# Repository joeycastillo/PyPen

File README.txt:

PyPen Project

Very WIP. See here: https://twitter.com/josecastillo/status/1503400227864301573

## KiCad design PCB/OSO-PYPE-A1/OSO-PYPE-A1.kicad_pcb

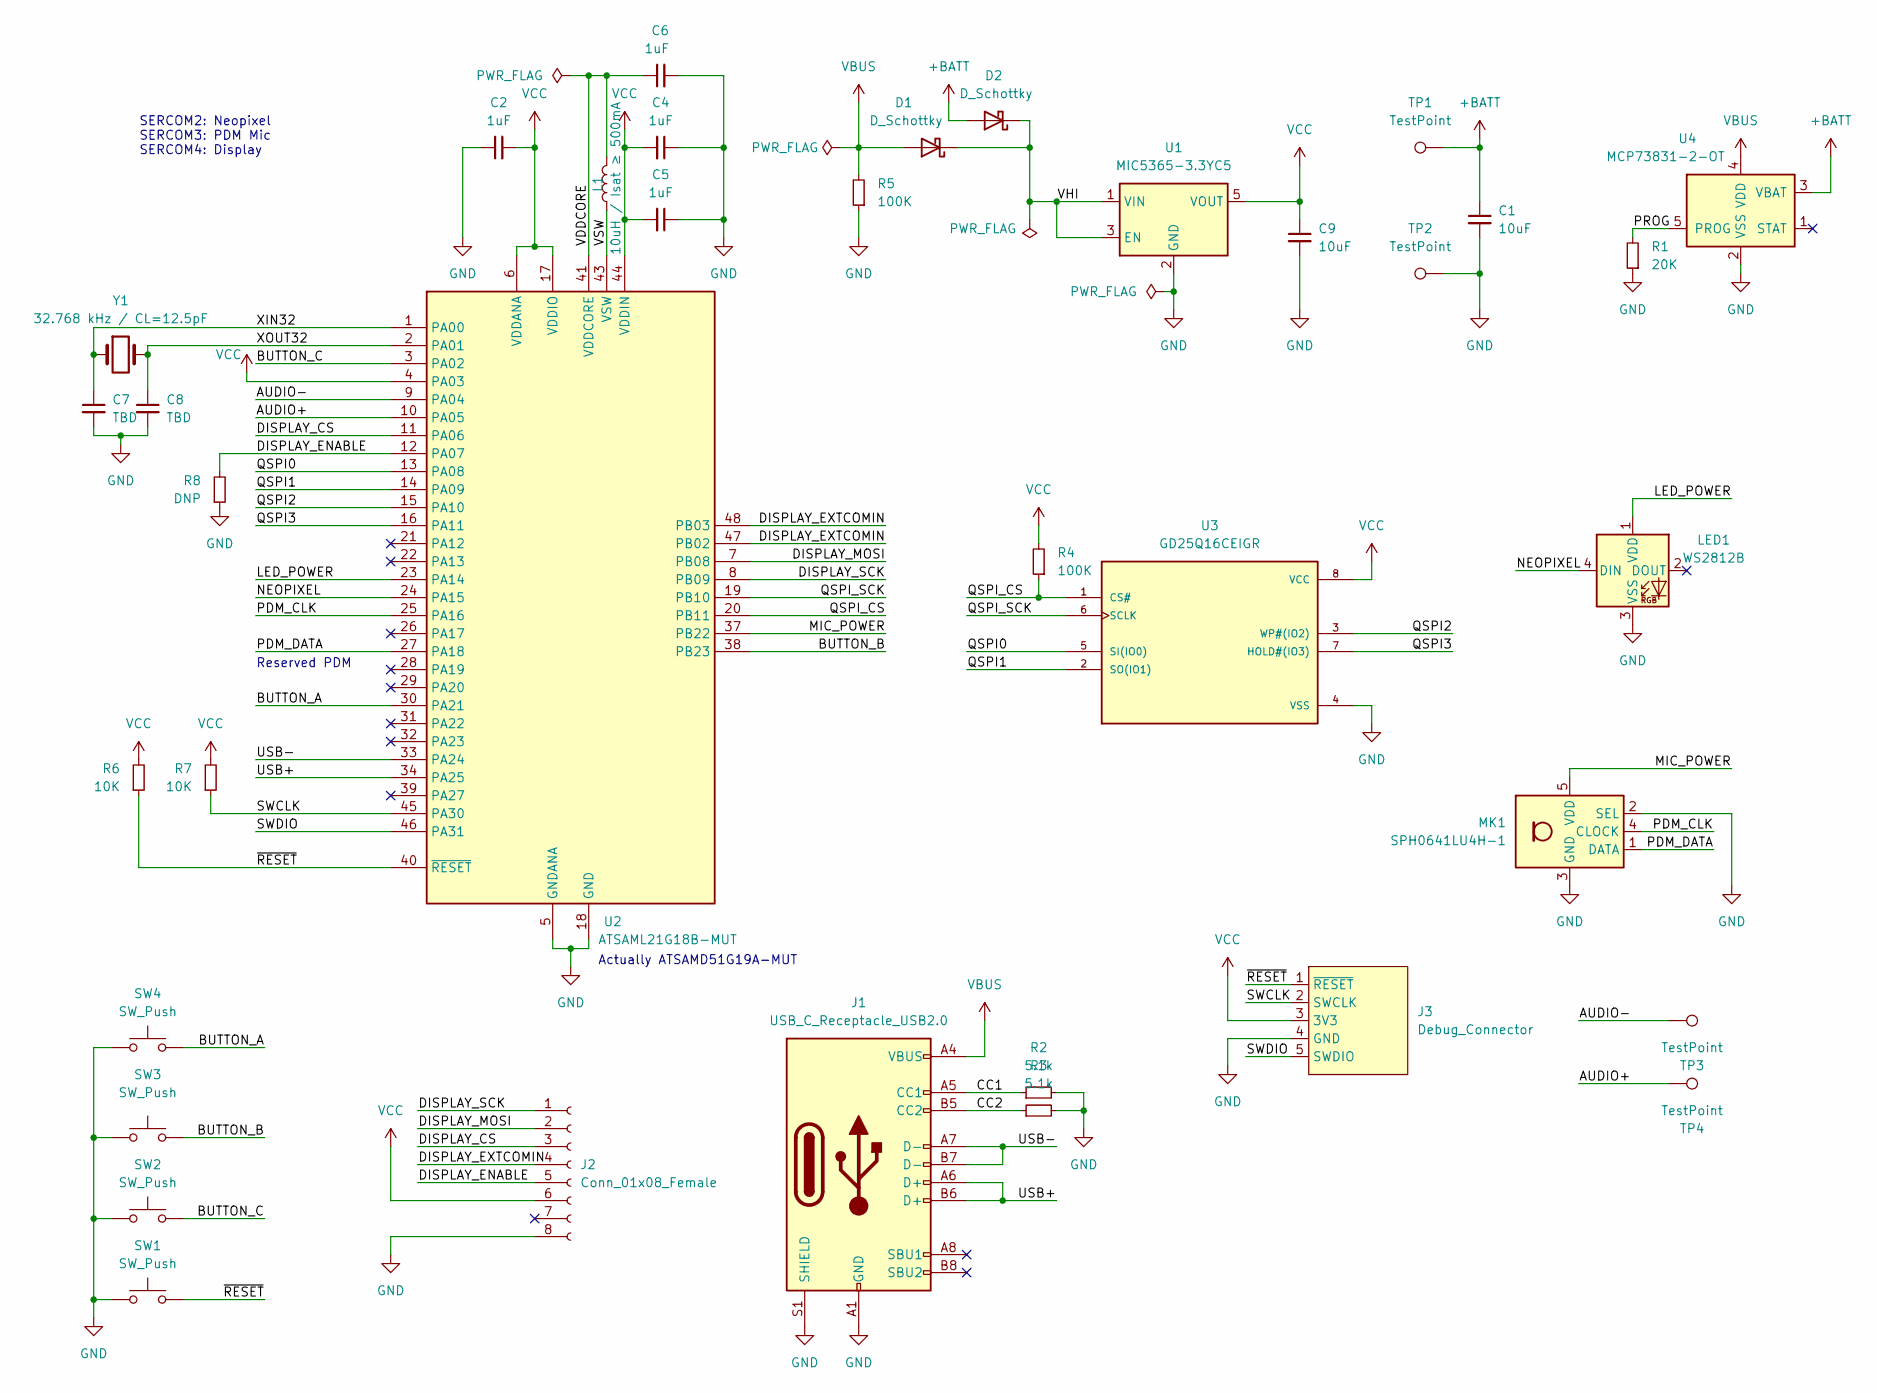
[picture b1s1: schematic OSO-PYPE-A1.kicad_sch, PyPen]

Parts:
C1, C9: 10uF; C_0603_1608Metric
C2, C4, C5, C6: 1uF; C_0603_1608Metric
C7, C8: TBD; C_0603_1608Metric
D1, D2: D_Schottky; D_SOD-323
J1: USB_C_Receptacle_USB2.0; USB_C_Receptacle_HRO_TYPE-C-31-M-12
J2: Conn_01x08_Female; TE_0-1734839-8_1x08-1MP_P0.5mm_Horizontal
J3: Debug_Connector; Debug_Connector_Stacked
L1: 10uH / Isat ≥ 500mA; L_0805_2012Metric
LED1: WS2812B; LED_WS2812B_2.0x2.0mm
MK1: SPH0641LU4H-1; Knowles_LGA-5_3.5x2.65mm
R1: 20K; R_0603_1608Metric
R2, R3: 5.1k; R_0603_1608Metric
R4, R5: 100K; R_0603_1608Metric
R6, R7: 10K; R_0603_1608Metric
R8: DNP; R_0603_1608Metric
SW1: SW_Push; Panasonic_EVQPUJ_EVQPUA
SW2, SW3, SW4: SW_Push; SW_Push_1P1T_NO_CK_KMR2
TP1, TP2: TestPoint; TestPoint_Keystone_5019_Minature
TP3, TP4: TestPoint; TestPoint_Pad_D1.0mm
U1: MIC5365-3.3YC5; SOT-353_SC-70-5
U2: ATSAML21G18B-MUT; QFN-48-1EP_7x7mm_P0.5mm_EP5.15x5.15mm
U3: GD25Q16CEIGR; PSON50P200X300X50-9N; PARTREV 3.0
U4: MCP73831-2-OT; SOT-23-5
Y1: 32.768 kHz / CL=12.5pF; Crystal_SMD_2012-2Pin_2.0x1.2mm

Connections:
+BATT: C1.1, D2.2 (A), TP1.1, U4.3 (VBAT)
/AUDIO+: TP4.1, U2.10 (PA05)
/AUDIO-: TP3.1, U2.9 (PA04)
/BUTTON_A: SW4.2, U2.30 (PA21)
/BUTTON_B: SW3.2, U2.38 (PB23)
/BUTTON_C: SW2.2, U2.3 (PA02)
/CC1: J1.A5 (CC1), R2.1
/CC2: J1.B5 (CC2), R3.1
/DISPLAY_CS: J2.3, U2.11 (PA06)
/DISPLAY_ENABLE: J2.5, R8.2, U2.12 (PA07)
/DISPLAY_EXTCOMIN: J2.4, U2.47 (PB02), U2.48 (PB03)
/DISPLAY_MOSI: J2.2, U2.7 (PB08)
/DISPLAY_SCK: J2.1, U2.8 (PB09)
/LED_POWER: LED1.1 (VDD), U2.23 (PA14)
/MIC_POWER: MK1.5 (VDD), U2.37 (PB22)
/NEOPIXEL: LED1.4 (DIN), U2.24 (PA15)
/PDM_CLK: MK1.4 (CLOCK), U2.25 (PA16)
/PDM_DATA: MK1.1 (DATA), U2.27 (PA18)
/PROG: R1.2, U4.5 (PROG)
/QSPI0: U2.13 (PA08), U3.5 (SI(IO0))
/QSPI1: U2.14 (PA09), U3.2 (SO(IO1))
/QSPI2: U2.15 (PA10), U3.3 (WP#(IO2))
/QSPI3: U2.16 (PA11), U3.7 (HOLD#(IO3))
/QSPI_CS: R4.1, U2.20 (PB11), U3.1 (CS#)
/QSPI_SCK: U2.19 (PB10), U3.6 (SCLK)
/SWCLK: J3.2 (SWCLK), R7.1, U2.45 (PA30)
/SWDIO: J3.5 (SWDIO), U2.46 (PA31)
/USB+: J1.A6 (D+), J1.B6 (D+), U2.34 (PA25)
/USB-: J1.A7 (D-), J1.B7 (D-), U2.33 (PA24)
/VDDCORE: C6.1, L1.2, U2.41 (VDDCORE)
/VHI: D1.1 (K), D2.1 (K), U1.1 (VIN), U1.3 (EN)
/VSW: L1.1, U2.43 (VSW)
/XIN32: C7.1, U2.1 (PA00), Y1.1
/XOUT32: C8.1, U2.2 (PA01), Y1.2
/~RESET: J3.1 (~RESET), R6.1, SW1.2, U2.40 (~RESET)
GND: C1.2, C2.1, C4.1, C5.1, C6.2, C7.2, C8.2, C9.2, J1.A1 (GND), J1.A12 (GND), J1.B1 (GND), J1.B12 (GND), J1.S1 (SHIELD), J2.8, J3.4 (GND), LED1.3 (VSS), MK1.2 (SEL), MK1.3 (GND), R1.1, R2.2, R3.2, R5.1, R8.1, SW1.1, SW2.1, SW3.1, SW4.1, TP2.1, U1.2 (GND), U2.5 (GNDANA), U2.18 (GND), U2.35 (GND), U2.42 (GND), U2.49, U3.4 (VSS), U4.2 (VSS)
VBUS: D1.2 (A), J1.A4 (VBUS), J1.A9 (VBUS), J1.B4 (VBUS), J1.B9 (VBUS), R5.2, U4.4 (VDD)
VCC: C2.2, C4.2, C5.2, C9.1, J2.6, J3.3 (3V3), R4.2, R6.2, R7.2, U1.5 (VOUT), U2.4 (PA03), U2.6 (VDDANA), U2.17 (VDDIO), U2.36 (VDDIO), U2.44 (VDDIN), U3.8 (VCC)

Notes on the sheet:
SERCOM2: Neopixel SERCOM3: PDM Mic SERCOM4: Display
Actually ATSAMD51G19A-MUT
Reserved PDM

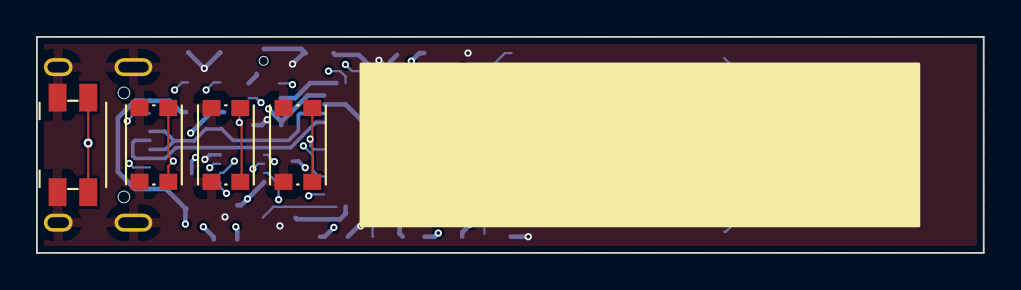
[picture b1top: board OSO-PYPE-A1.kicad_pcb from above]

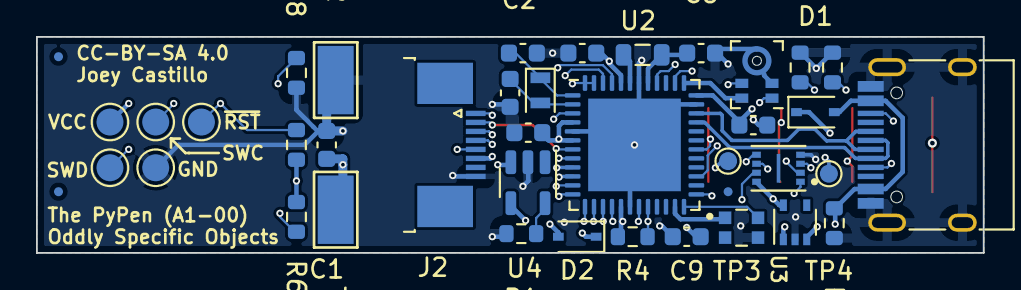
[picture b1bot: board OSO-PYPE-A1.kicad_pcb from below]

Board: 6 copper layers, 52.6 x 12.0 mm, 37 parts (33 on the bottom side), 38 nets.

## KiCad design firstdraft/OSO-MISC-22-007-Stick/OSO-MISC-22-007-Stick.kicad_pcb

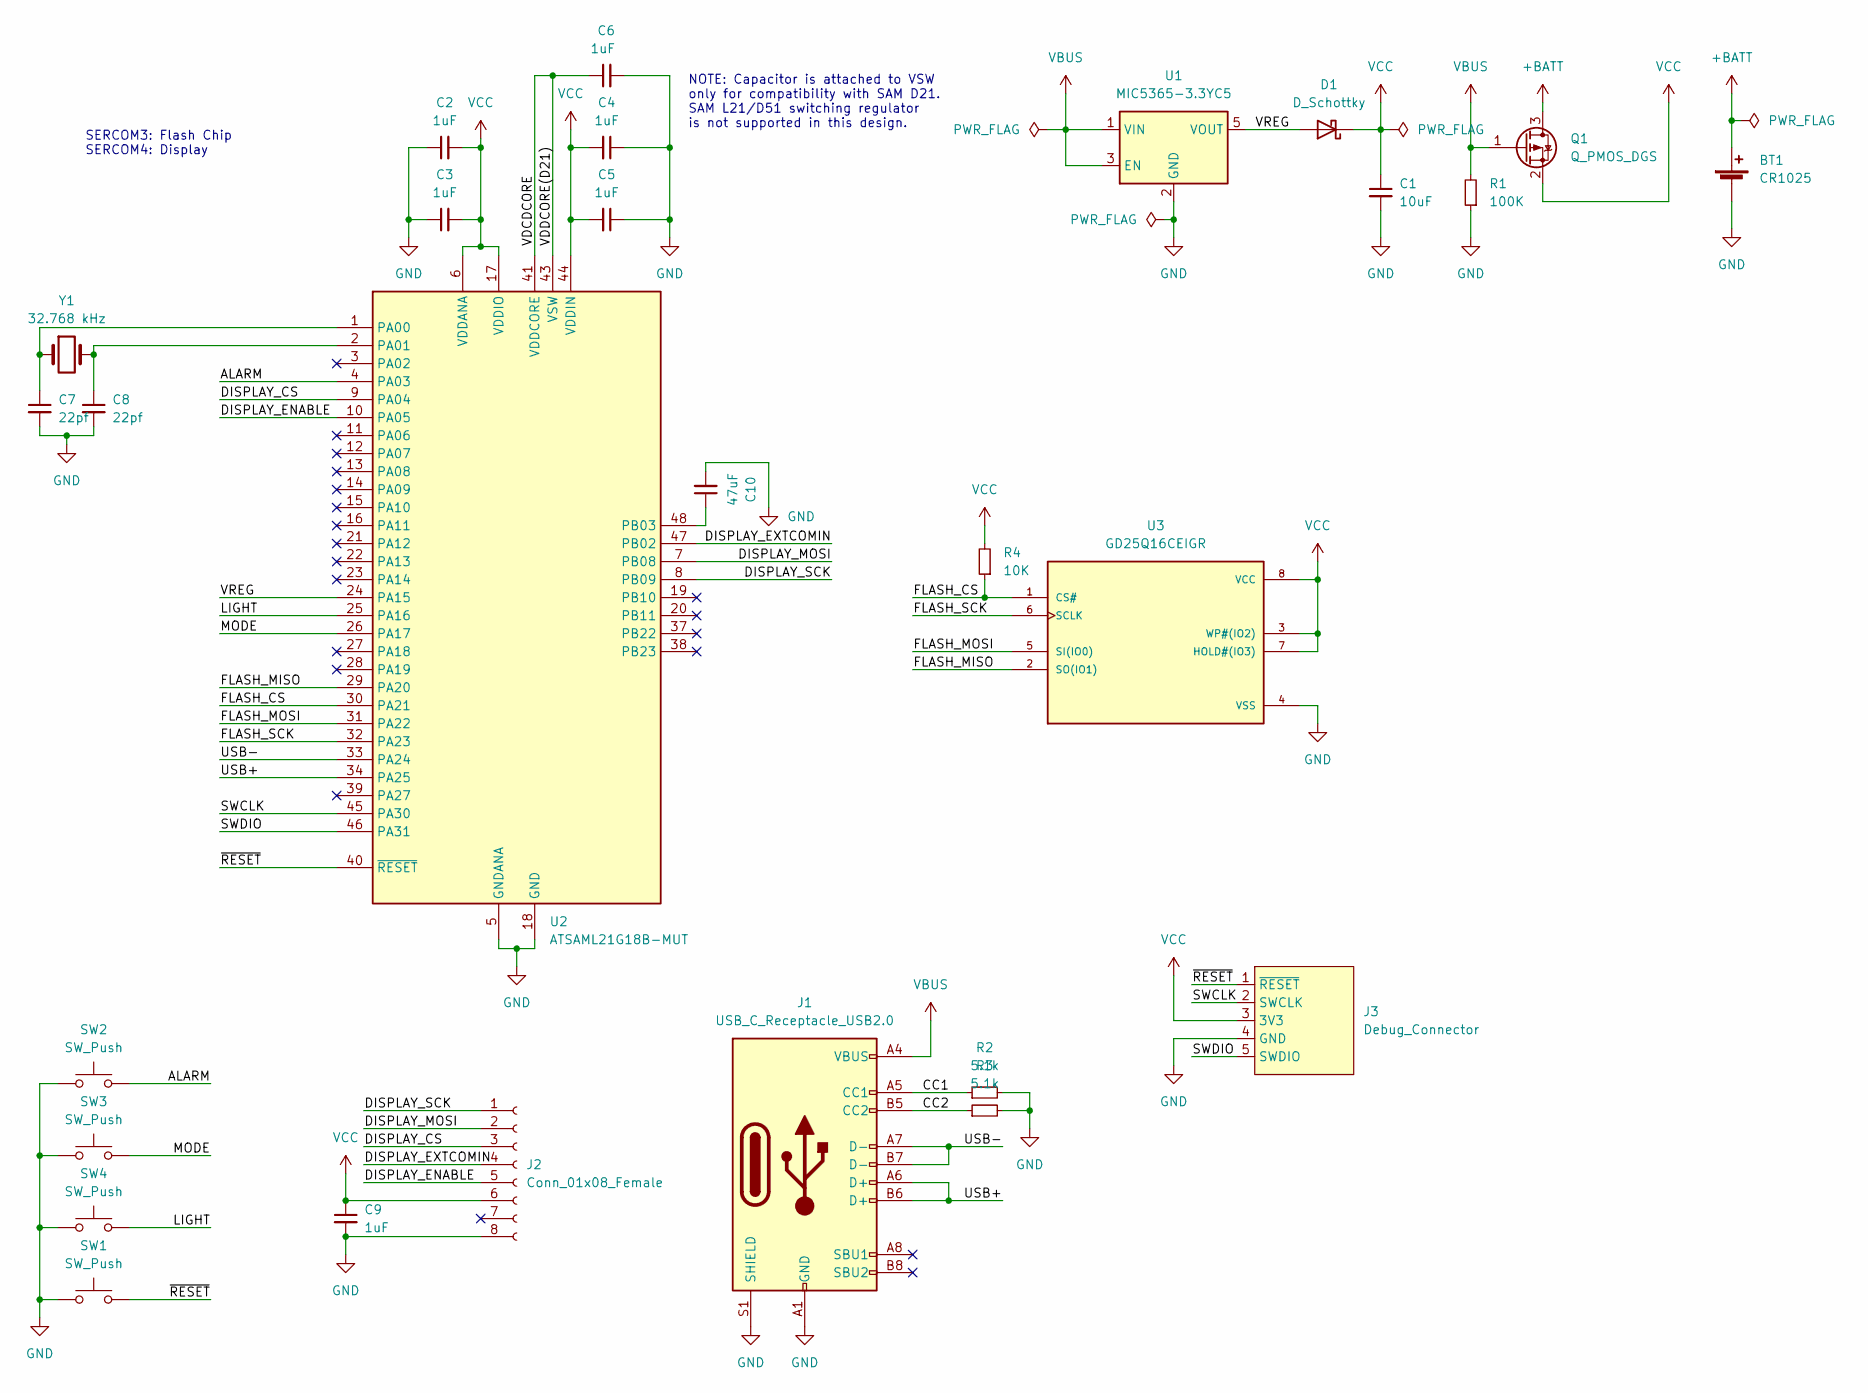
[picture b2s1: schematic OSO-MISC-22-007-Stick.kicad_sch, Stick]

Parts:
BT1: CR1025; KEYSTONE_3030_3050
C1: 10uF; C_0603_1608Metric
C2, C3, C4, C5, C6, C9: 1uF; C_0603_1608Metric
C7, C8: 22pf; C_0603_1608Metric
C10: 47uF; C_0603_1608Metric
D1: D_Schottky; D_SOD-323
J1: USB_C_Receptacle_USB2.0; USB_C_Receptacle_HRO_TYPE-C-31-M-12
J2: Conn_01x08_Female; TE_0-1734839-8_1x08-1MP_P0.5mm_Horizontal
J3: Debug_Connector; Debug_Connector_Straight
Q1: Q_PMOS_DGS; SOT-323_SC-70
R1: 100K; R_0603_1608Metric
R2, R3: 5.1k; R_0603_1608Metric
R4: 10K; R_0603_1608Metric
SW1: SW_Push; Panasonic_EVQPUJ_EVQPUA
SW2, SW3, SW4: SW_Push; SW_Push_1P1T_NO_CK_KMR2
U1: MIC5365-3.3YC5; SOT-353_SC-70-5
U2: ATSAML21G18B-MUT; QFN-48-1EP_7x7mm_P0.5mm_EP5.15x5.15mm
U3: GD25Q16CEIGR; PSON50P200X300X50-9N; PARTREV 3.0
Y1: 32.768 kHz; Crystal_SMD_3215-2Pin_3.2x1.5mm

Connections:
+BATT: BT1.1 (+), Q1.3 (D)
/ALARM: SW2.2, U2.4 (PA03)
/CC1: J1.A5 (CC1), R2.1
/CC2: J1.B5 (CC2), R3.1
/DISPLAY_CS: J2.3, U2.9 (PA04)
/DISPLAY_ENABLE: J2.5, U2.10 (PA05)
/DISPLAY_EXTCOMIN: J2.4, U2.47 (PB02)
/DISPLAY_MOSI: J2.2, U2.7 (PB08)
/DISPLAY_SCK: J2.1, U2.8 (PB09)
/FLASH_CS: R4.1, U2.30 (PA21), U3.1 (CS#)
/FLASH_MISO: U2.29 (PA20), U3.2 (SO(IO1))
/FLASH_MOSI: U2.31 (PA22), U3.5 (SI(IO0))
/FLASH_SCK: U2.32 (PA23), U3.6 (SCLK)
/LIGHT: SW4.2, U2.25 (PA16)
/MODE: SW3.2, U2.26 (PA17)
/SWCLK: J3.2 (SWCLK), U2.45 (PA30)
/SWDIO: J3.5 (SWDIO), U2.46 (PA31)
/USB+: J1.A6 (D+), J1.B6 (D+), U2.34 (PA25)
/USB-: J1.A7 (D-), J1.B7 (D-), U2.33 (PA24)
/VDCDCORE: C6.1, U2.41 (VDDCORE), U2.43 (VSW)
/VREG: D1.2 (A), U1.5 (VOUT), U2.24 (PA15)
/~RESET: J3.1 (~RESET), SW1.2, U2.40 (~RESET)
GND: BT1.2 (-), C1.2, C2.1, C3.1, C4.1, C5.1, C6.2, C7.2, C8.2, C9.2, C10.2, J1.A1 (GND), J1.A12 (GND), J1.B1 (GND), J1.B12 (GND), J1.S1 (SHIELD), J2.8, J3.4 (GND), R1.1, R2.2, R3.2, SW1.1, SW2.1, SW3.1, SW4.1, U1.2 (GND), U2.5 (GNDANA), U2.18 (GND), U2.35 (GND), U2.42 (GND), U2.49, U3.4 (VSS)
unnamed: C7.1, U2.1 (PA00), Y1.1
unnamed: C8.1, U2.2 (PA01), Y1.2
unnamed: C10.1, U2.48 (PB03)
VBUS: J1.A4 (VBUS), J1.A9 (VBUS), J1.B4 (VBUS), J1.B9 (VBUS), Q1.1 (G), R1.2, U1.1 (VIN), U1.3 (EN)
VCC: C1.1, C2.2, C3.2, C4.2, C5.2, C9.1, D1.1 (K), J2.6, J3.3 (3V3), Q1.2 (S), R4.2, U2.6 (VDDANA), U2.17 (VDDIO), U2.36 (VDDIO), U2.44 (VDDIN), U3.3 (WP#(IO2)), U3.7 (HOLD#(IO3)), U3.8 (VCC)

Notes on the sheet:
SERCOM3: Flash Chip SERCOM4: Display
NOTE: Capacitor is attached to VSW only for compatibility with SAM D21. SAM L21/D51 switching regulator is not supported in this design.

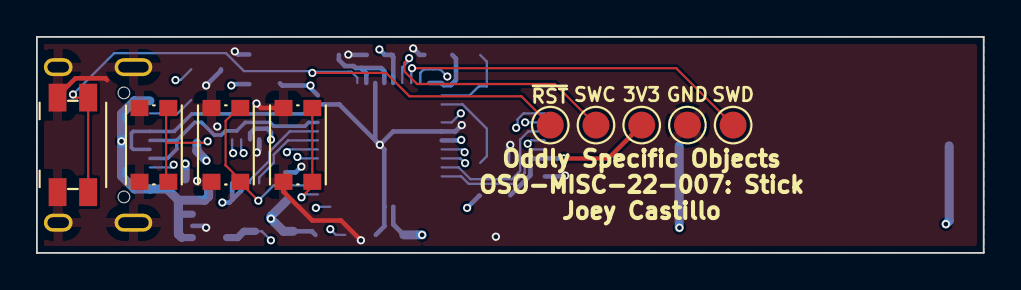
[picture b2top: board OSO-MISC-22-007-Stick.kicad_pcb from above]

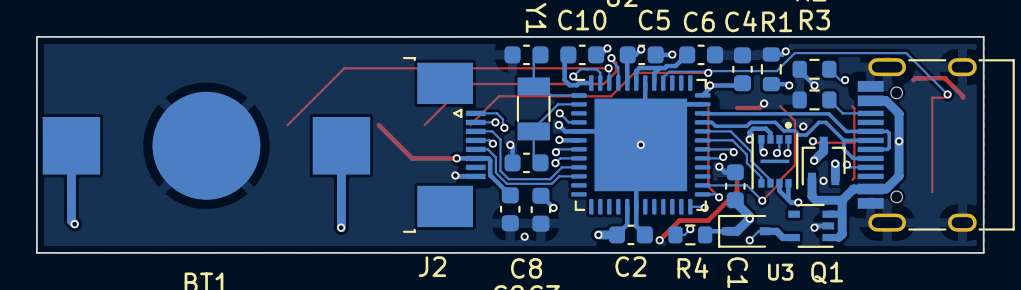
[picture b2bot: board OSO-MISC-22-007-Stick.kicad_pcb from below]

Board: 4 copper layers, 52.6 x 12.0 mm, 28 parts (23 on the bottom side), 28 nets.

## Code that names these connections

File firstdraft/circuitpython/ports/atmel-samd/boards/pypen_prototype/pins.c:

#include "shared-bindings/board/__init__.h"

STATIC const mp_rom_map_elem_t board_module_globals_table[] = {
    CIRCUITPYTHON_BOARD_DICT_STANDARD_ITEMS

    { MP_ROM_QSTR(MP_QSTR_BTN_ALARM), MP_ROM_PTR(&pin_PA03) },
    { MP_ROM_QSTR(MP_QSTR_BTN_LIGHT), MP_ROM_PTR(&pin_PA16) },
    { MP_ROM_QSTR(MP_QSTR_BTN_MODE), MP_ROM_PTR(&pin_PA17) },
    { MP_ROM_QSTR(MP_QSTR_VREG), MP_ROM_PTR(&pin_PA15) },
    { MP_ROM_QSTR(MP_QSTR_DISPLAY_CS),  MP_ROM_PTR(&pin_PA04) },
    { MP_ROM_QSTR(MP_QSTR_DISPLAY_ENABLE),  MP_ROM_PTR(&pin_PA05) },
    { MP_ROM_QSTR(MP_QSTR_DISPLAY_EXTCOMIN),  MP_ROM_PTR(&pin_PB02) },
    { MP_ROM_QSTR(MP_QSTR_SCK),  MP_ROM_PTR(&pin_PB09) },
    { MP_ROM_QSTR(MP_QSTR_MOSI), MP_ROM_PTR(&pin_PB08) },
    { MP_ROM_QSTR(MP_QSTR_MISO), MP_ROM_PTR(&pin_PB10) },
    { MP_ROM_QSTR(MP_QSTR_SPI), MP_ROM_PTR(&board_spi_obj) },
};
MP_DEFINE_CONST_DICT(board_module_globals, board_module_globals_table);

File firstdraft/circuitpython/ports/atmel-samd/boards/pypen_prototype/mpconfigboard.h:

#define MICROPY_HW_BOARD_NAME "PyPen Prototype"
#define MICROPY_HW_MCU_NAME "samd21g18"

#define MICROPY_HW_LED_STATUS   (&pin_PA17)

#define SPI_FLASH_BAUDRATE  (8000000)

#define SPI_FLASH_MOSI_PIN          &pin_PA22
#define SPI_FLASH_MISO_PIN          &pin_PA20
#define SPI_FLASH_SCK_PIN           &pin_PA23
#define SPI_FLASH_CS_PIN            &pin_PA21

#define BOARD_HAS_CRYSTAL 0

#define DEFAULT_SPI_BUS_SCK (&pin_PB09)
#define DEFAULT_SPI_BUS_MOSI (&pin_PB08)
#define DEFAULT_SPI_BUS_MISO (&pin_PB10)

// These pins are connected to the external crystal.
#define IGNORE_PIN_PA00     1
#define IGNORE_PIN_PA01     1

// USB is always used internally so skip the pin objects for it.
#define IGNORE_PIN_PA24     1
#define IGNORE_PIN_PA25     1

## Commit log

2022-03-26 second draft

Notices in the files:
PCB/OSO-PYPE-A1/OSO-PYPE-A1.kicad_pcb:
CC-BY-SA 4.0
